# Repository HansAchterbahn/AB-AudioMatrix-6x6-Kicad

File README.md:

# AB AudioMatrix 6×6

Active audio matrix (6×6), that can map 6 input channels (1-6) to 6 output channels (A-F). Connection via 3.5 jack cable. Compatible with line signals, aux, headphones and active speakers. Each output channel can map one input channel at a time.

*Fork me and have fun!*

## 1 Content and Structure

| File / Folder                 | Abbreviation     | Description                                                                             |
| ----------------------------- | ---------------- | --------------------------------------------------------------------------------------- |
| /3d/                          | 3D models        | Files to work with in a 3D CAD program                                                  |
| /bom/                         | Bill of Material | Files with needed components and corresponding order number from different distributors |
| /case/                        | Case for PCB     | Files with an example case for the PCBs                                                 |
| /doc/                         | Documentation    | Files needed in README.md to document the repository                                    |
| /gerber/                      | Gerber files     | Files exported from Board Layout to order the PCBs from a manufacturer                  |
| /sch/                         | Schematic        | Additional schematic files                                                              |
| /AB-AudioMatrix-6x6.pro       | —                | Kicad Project File                                                                      |
| /AB-AudioMatrix-6x6.sch       | —                | Root schematic files                                                                    |
| /AB-AudioMatrix-6x6.kicad_pcb | —                | PCB / Board Layout File                                                                 |
| /LICENSE.md                   | —                | File contains project license                                                           |
| /README.md                    | —                | Markdown file with the documentation you are reading now                                |

## 2 Power Supply Modes

| Mode       | +             | —             | ⊥   | Jumper JP1 | U7, R25, R26  | Info                                                              |
| ---------- | ------------- | ------------- | --- | ---------- | ------------- | ----------------------------------------------------------------- |
| Symmetric  | +2.5 to +15 V | -2.5 to -15 V | 0V  | Open       | not necessary | Highly recommended for good Sound and clearly separated channels  |
| Asymmetric | +5 to +30 V   | 0 V           | --- | Closed     | necessary     | Possible, but not recommended; Channels are not clearly separated |

## 3 Pictures

### 3.1 Mounted device

Front view

Rear view

Bottom view

### 3.2 Board

Top view

Rear view

<!--
## 4 CAD Data

Top view

Front view

Rear view

Bottom view
-->

## 4 Schematic

Sheet 1: Root / Overview Page

Sheet 2: Switches and OPAs

Sheet 3: Audio Input and Output

## 5 Board Layout

PCB / Board layout

## 6 License

<p xmlns:dct="http://purl.org/dc/terms/" xmlns:cc="http://creativecommons.org/ns#" class="license-text"><a rel="cc:attributionURL" href="https://github.com/HansAchterbahn/AB-AudioMatrix-6x6"><span rel="dct:title">AB AudioMatrix 6×6</span></a> by <a rel="cc:attributionURL" href="https://github.com/HansAchterbahn/"><span rel="cc:attributionName">Hans Achterbahn </span></a>CC BY 4.0 </p>

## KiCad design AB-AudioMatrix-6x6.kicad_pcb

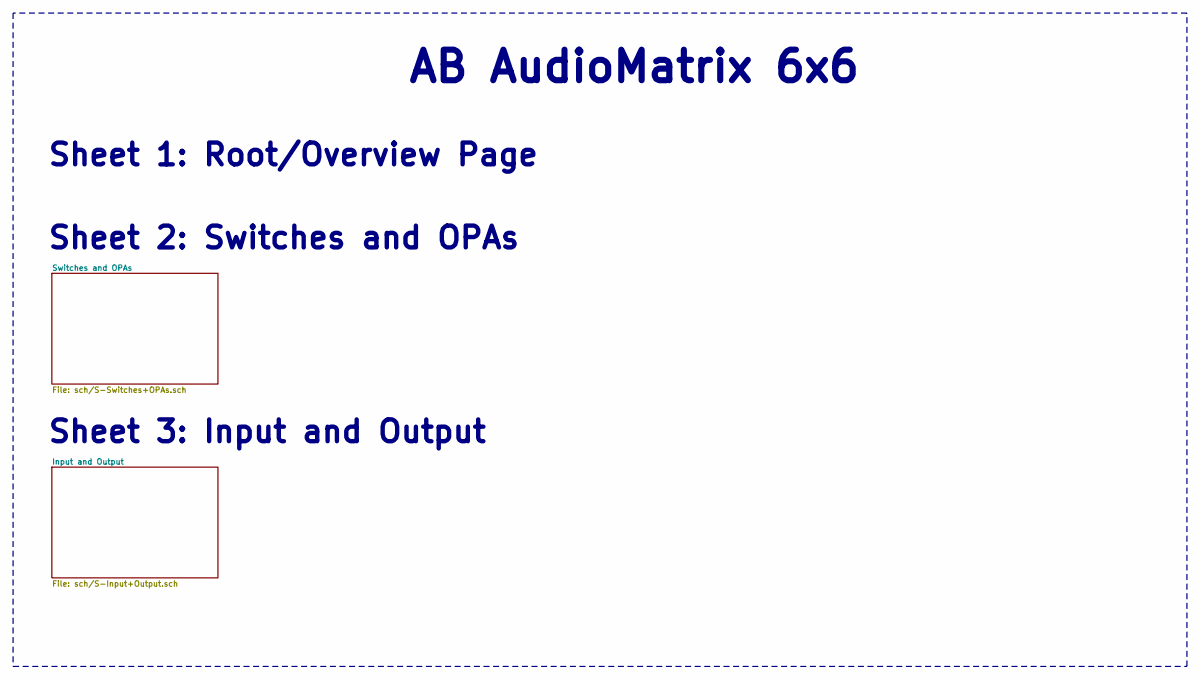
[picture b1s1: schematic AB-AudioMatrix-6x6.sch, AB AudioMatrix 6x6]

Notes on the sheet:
AB AudioMatrix 6x6
Sheet 3: Input and Output
Sheet 2: Switches and OPAs
Sheet 1: Root/Overview Page

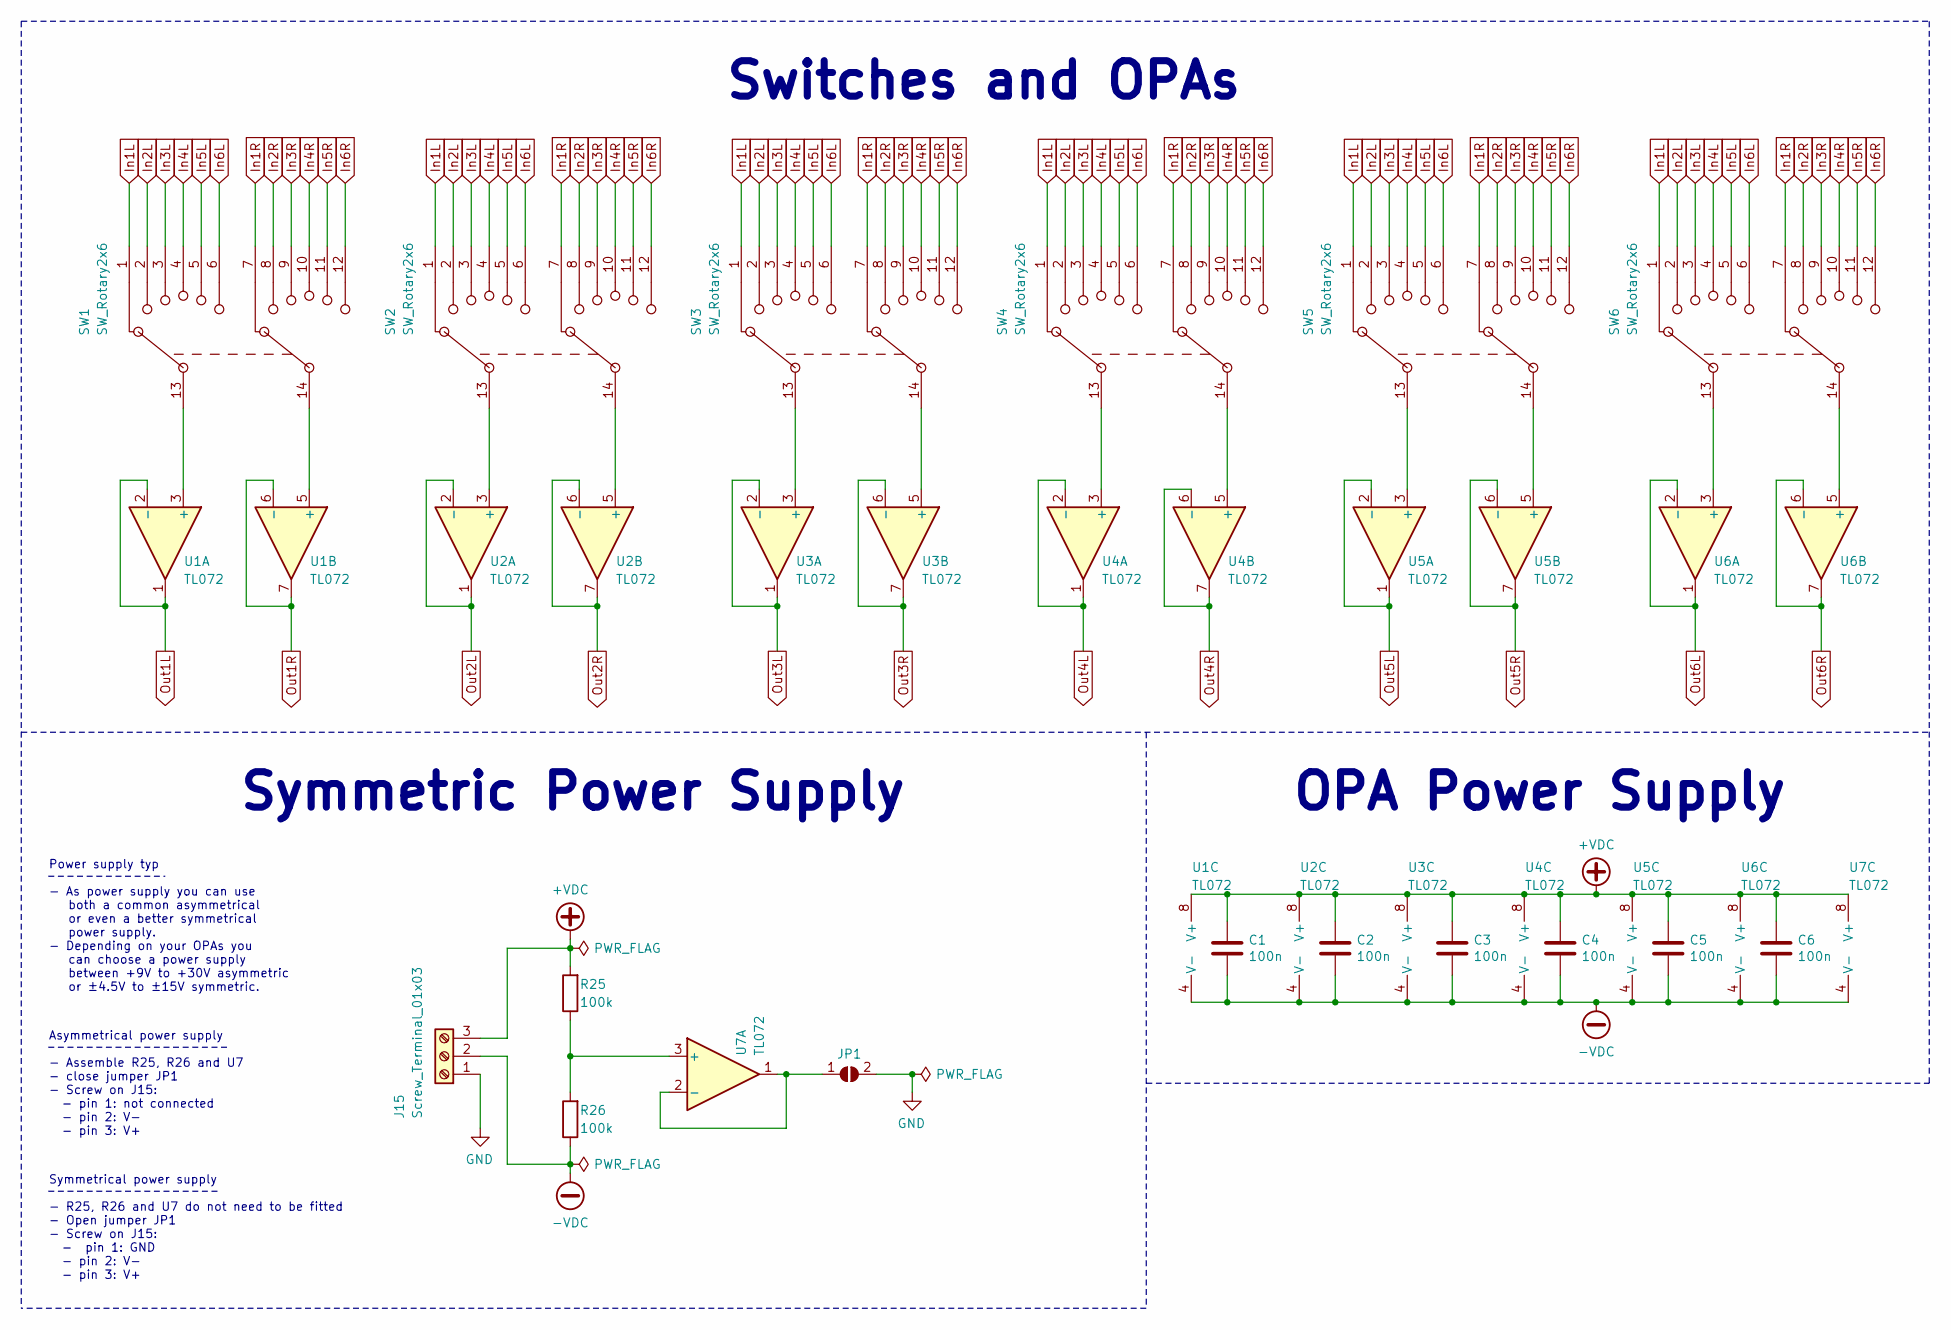
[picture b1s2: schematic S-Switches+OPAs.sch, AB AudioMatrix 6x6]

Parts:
C1, C2, C3, C4, C5, C6: 100n; C_0603_1608Metric_Pad1.05x0.95mm_HandSolder; Digi-Key 311-1779-1-ND
J15: Screw_Terminal_01x03; Wuerth-691102710003; Digi-Key 732-2029-ND
JP1: SolderJumper_2_Open; SolderJumper-2_P1.3mm_Open_TrianglePad1.0x1.5mm; Digi-Key —
R25, R26: 100k; R_0603_1608Metric_Pad1.05x0.95mm_HandSolder; Digi-Key 541-3950-1-ND
SW1, SW2, SW3, SW4, SW5, SW6: SW_Rotary2x6; CK102X06; Digi-Key —
U1, U2, U3, U4, U5, U6, U7: TL072; SOIC-8_3.9x4.9mm_P1.27mm; Digi-Key 296-1282-2-ND

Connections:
+VDC: C1.1, C2.1, C3.1, C4.1, C5.1, C6.1, J15.3, R25.2, U1.8 (V+), U2.8 (V+), U3.8 (V+), U4.8 (V+), U5.8 (V+), U6.8 (V+), U7.8 (V+)
-VDC: C1.2, C2.2, C3.2, C4.2, C5.2, C6.2, J15.2, R26.1, U1.4 (V-), U2.4 (V-), U3.4 (V-), U4.4 (V-), U5.4 (V-), U6.4 (V-), U7.4 (V-)
GND: J15.1, JP1.2 (B); also elsewhere on the board
In1L: SW1.1, SW2.1, SW3.1, SW4.1, SW5.1, SW6.1; also elsewhere on the board
In1R: SW1.7, SW2.7, SW3.7, SW4.7, SW5.7, SW6.7; also elsewhere on the board
In2L: SW1.2, SW2.2, SW3.2, SW4.2, SW5.2, SW6.2; also elsewhere on the board
In2R: SW1.8, SW2.8, SW3.8, SW4.8, SW5.8, SW6.8; also elsewhere on the board
In3L: SW1.3, SW2.3, SW3.3, SW4.3, SW5.3, SW6.3; also elsewhere on the board
In3R: SW1.9, SW2.9, SW3.9, SW4.9, SW5.9, SW6.9; also elsewhere on the board
In4L: SW1.4, SW2.4, SW3.4, SW4.4, SW5.4, SW6.4; also elsewhere on the board
In4R: SW1.10, SW2.10, SW3.10, SW4.10, SW5.10, SW6.10; also elsewhere on the board
In5L: SW1.5, SW2.5, SW3.5, SW4.5, SW5.5, SW6.5; also elsewhere on the board
In5R: SW1.11, SW2.11, SW3.11, SW4.11, SW5.11, SW6.11; also elsewhere on the board
In6L: SW1.6, SW2.6, SW3.6, SW4.6, SW5.6, SW6.6; also elsewhere on the board
In6R: SW1.12, SW2.12, SW3.12, SW4.12, SW5.12, SW6.12; also elsewhere on the board
unnamed: JP1.1 (A), U7.1, U7.2 (-)
unnamed: R25.1, R26.2, U7.3 (+)
unnamed: SW1.13, U1.3 (+)
unnamed: SW1.14, U1.5 (+)
unnamed: SW2.13, U2.3 (+)
unnamed: SW2.14, U2.5 (+)
unnamed: SW3.13, U3.3 (+)
unnamed: SW3.14, U3.5 (+)
unnamed: SW4.13, U4.3 (+)
unnamed: SW4.14, U4.5 (+)
unnamed: SW5.13, U5.3 (+)
unnamed: SW5.14, U5.5 (+)
unnamed: SW6.13, U6.3 (+)
unnamed: SW6.14, U6.5 (+)
Out1L: U1.1, U1.2 (-); also elsewhere on the board
Out1R: U1.6 (-), U1.7; also elsewhere on the board
Out2L: U2.1, U2.2 (-); also elsewhere on the board
Out2R: U2.6 (-), U2.7; also elsewhere on the board
Out3L: U3.1, U3.2 (-); also elsewhere on the board
Out3R: U3.6 (-), U3.7; also elsewhere on the board
Out4L: U4.1, U4.2 (-); also elsewhere on the board
Out4R: U4.6 (-), U4.7; also elsewhere on the board
Out5L: U5.1, U5.2 (-); also elsewhere on the board
Out5R: U5.6 (-), U5.7; also elsewhere on the board
Out6L: U6.1, U6.2 (-); also elsewhere on the board
Out6R: U6.6 (-), U6.7; also elsewhere on the board

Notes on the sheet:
Switches and OPAs
OPA Power Supply
Symmetric Power Supply
Symmetrical power supply - R25, R26 and U7 do not need to be fitted - Open jumper JP1 - Screw on J15: - pin 1: GND - pin 2: V- - pin 3: V+
Asymmetrical power supply - Assemble R25, R26 and U7 - close jumper JP1 - Screw on J15: - pin 1: not connected - pin 2: V- - pin 3: V+
Power supply typ - As power supply you can use both a common asymmetrical or even a better symmetrical power supply. - Depending on your OPAs you can choose a power supply between +9V to +30V asymmetric or ±4.5V to ±15V symmetric.

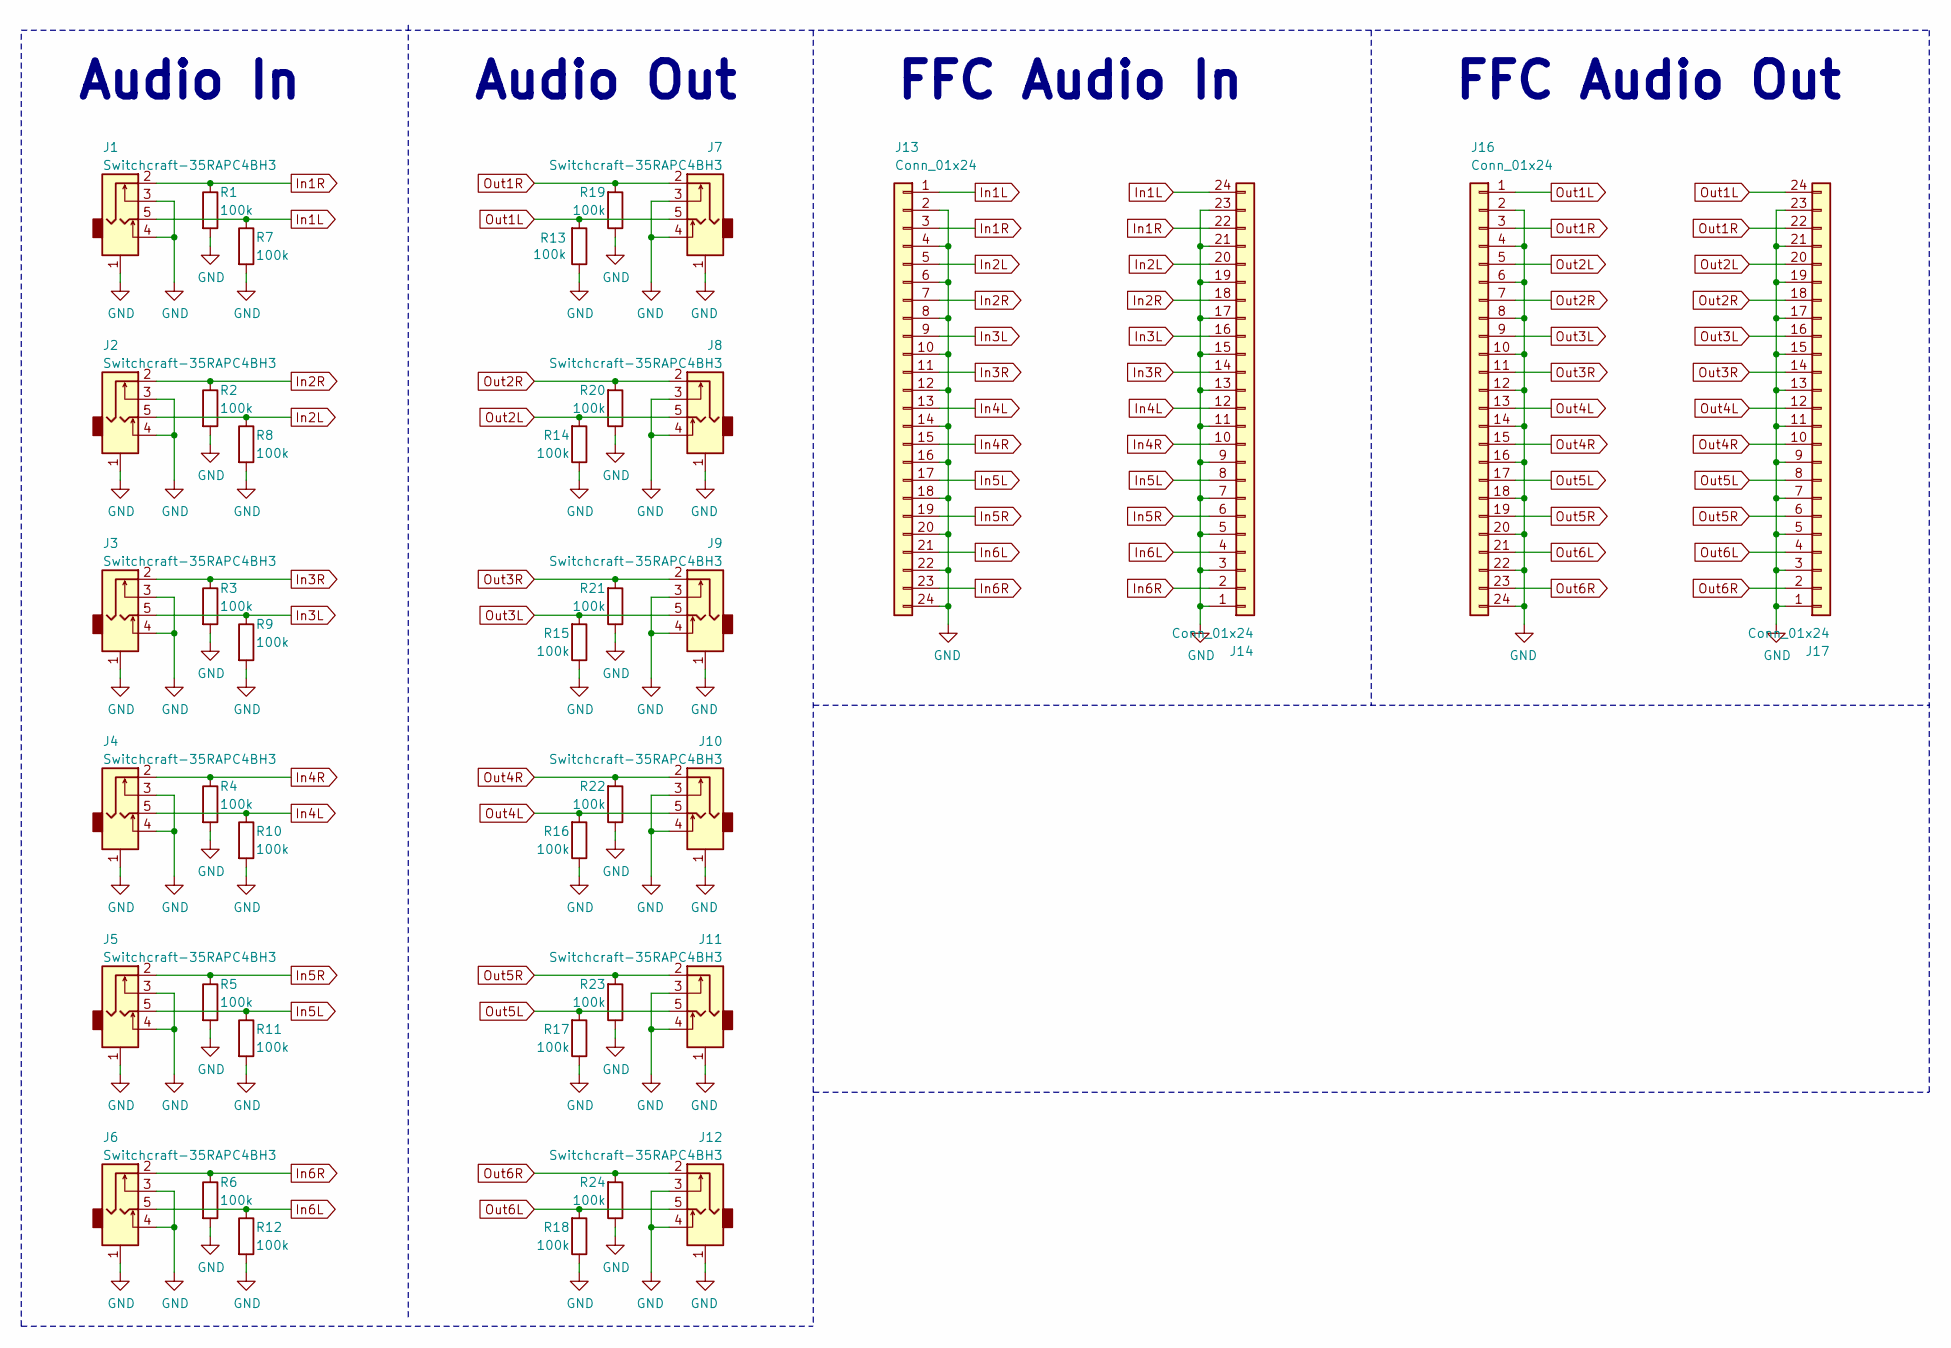
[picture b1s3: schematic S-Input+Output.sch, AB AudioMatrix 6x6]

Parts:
J1, J2, J3, J4, J5, J6, J7, J8, J9, J10, J11, J12: Switchcraft-35RAPC4BH3; Digi-Key SC1464-ND
J13, J14, J16, J17: Conn_01x24; Wuerth-686124188622; Digi-Key 732-686124188622CT-ND
R1, R2, R3, R4, R5, R6, R7, R8, R9, R10, R11, R12, R13, R14, R15, R16, R17, R18, R19, R20, R21, R22, R23, R24: 100k; R_0603_1608Metric_Pad1.05x0.95mm_HandSolder; Digi-Key 541-3950-1-ND

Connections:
GND: J1.1, J1.3, J1.4, J2.1, J2.3, J2.4, J3.1, J3.3, J3.4, J4.1, J4.3, J4.4, J5.1, J5.3, J5.4, J6.1, J6.3, J6.4, J7.1, J7.3, J7.4, J8.1, J8.3, J8.4, J9.1, J9.3, J9.4, J10.1, J10.3, J10.4, J11.1, J11.3, J11.4, J12.1, J12.3, J12.4, J13.2, J13.4, J13.6, J13.8, J13.10, J13.12, J13.14, J13.16, J13.18, J13.20, J13.22, J13.24, J14.1, J14.3, J14.5, J14.7, J14.9, J14.11, J14.13, J14.15, J14.17, J14.19, J14.21, J14.23, J16.2, J16.4, J16.6, J16.8, J16.10, J16.12, J16.14, J16.16, J16.18, J16.20, J16.22, J16.24, J17.1, J17.3, J17.5, J17.7, J17.9, J17.11, J17.13, J17.15, J17.17, J17.19, J17.21, J17.23, R1.2, R2.2, R3.2, R4.2, R5.2, R6.2, R7.2, R8.2, R9.2, R10.2, R11.2, R12.2, R13.1, R14.1, R15.1, R16.1, R17.1, R18.1, R19.1, R20.1, R21.1, R22.1, R23.1, R24.1; also elsewhere on the board
In1L: J1.5, J13.1, J14.24, R7.1; also elsewhere on the board
In1R: J1.2, J13.3, J14.22, R1.1; also elsewhere on the board
In2L: J2.5, J13.5, J14.20, R8.1; also elsewhere on the board
In2R: J2.2, J13.7, J14.18, R2.1; also elsewhere on the board
In3L: J3.5, J13.9, J14.16, R9.1; also elsewhere on the board
In3R: J3.2, J13.11, J14.14, R3.1; also elsewhere on the board
In4L: J4.5, J13.13, J14.12, R10.1; also elsewhere on the board
In4R: J4.2, J13.15, J14.10, R4.1; also elsewhere on the board
In5L: J5.5, J13.17, J14.8, R11.1; also elsewhere on the board
In5R: J5.2, J13.19, J14.6, R5.1; also elsewhere on the board
In6L: J6.5, J13.21, J14.4, R12.1; also elsewhere on the board
In6R: J6.2, J13.23, J14.2, R6.1; also elsewhere on the board
Out1L: J7.5, J16.1, J17.24, R13.2; also elsewhere on the board
Out1R: J7.2, J16.3, J17.22, R19.2; also elsewhere on the board
Out2L: J8.5, J16.5, J17.20, R14.2; also elsewhere on the board
Out2R: J8.2, J16.7, J17.18, R20.2; also elsewhere on the board
Out3L: J9.5, J16.9, J17.16, R15.2; also elsewhere on the board
Out3R: J9.2, J16.11, J17.14, R21.2; also elsewhere on the board
Out4L: J10.5, J16.13, J17.12, R16.2; also elsewhere on the board
Out4R: J10.2, J16.15, J17.10, R22.2; also elsewhere on the board
Out5L: J11.5, J16.17, J17.8, R17.2; also elsewhere on the board
Out5R: J11.2, J16.19, J17.6, R23.2; also elsewhere on the board
Out6L: J12.5, J16.21, J17.4, R18.2; also elsewhere on the board
Out6R: J12.2, J16.23, J17.2, R24.2; also elsewhere on the board

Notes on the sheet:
Audio In
Audio Out
FFC Audio In
FFC Audio Out

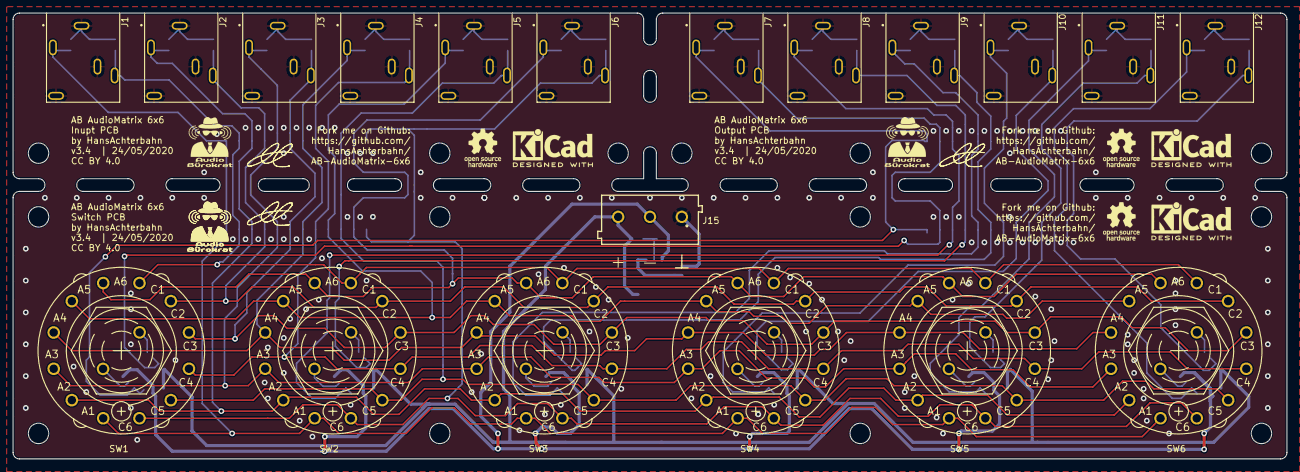
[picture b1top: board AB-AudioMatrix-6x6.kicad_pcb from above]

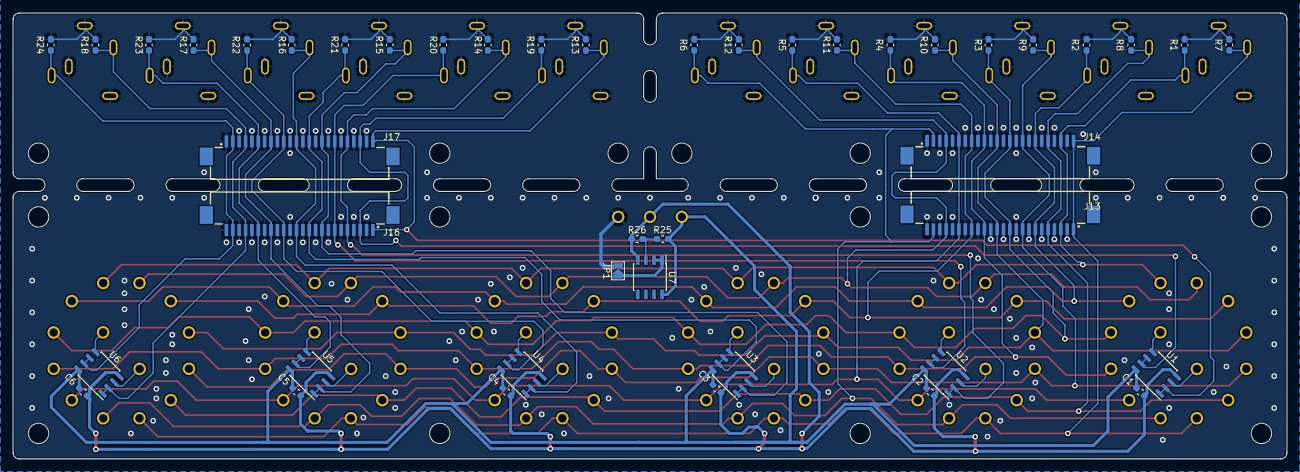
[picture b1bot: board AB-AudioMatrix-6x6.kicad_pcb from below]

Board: 4 copper layers, 200.0 x 70.0 mm, 63 parts (44 on the bottom side), 41 nets.

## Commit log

2020-05-12 Complete schematic | started PCB
2020-05-12 Added README and LICENCE
2020-05-13 added Edge.Cuts | devices arranged on PCB | added GND planes
2020-05-14 added converter for asymmetric power supply | Routing In & Out PCB finished | Routing Switch PCB started
2020-05-16 Routing switches complete
2020-05-16 Routing Input FFC connector to switches
2020-05-17 swaped supply pins | routing complete → routing revision and optimization necessary
2020-05-18 finished routing | added GND polygon | added description in surface plot | added pictures to README.md documentation | changed LICENCE.md to CC BY 4.0
2020-05-18 added gitignore
2020-05-18 Date updated and Github link added to schematic and board
2020-05-24 added new attributes MF, MFN, Mouser, Digi-Key, RS-Online, Infopage, datasheet | bill of material (BOM) created | infobox updated | added AudioBürokrat logo on silkscreen
2020-05-24 Added BOM files in .gitignore
2020-05-25 changed AudioBürokrat logo
2020-05-25 removed unwanted files
2020-05-25 added folder for BOM
2020-05-25 changed AudioBürokrat logo (Bitmap import)
2020-05-25 renamed doku folder to doc |updated README.md and some pictures in doc folder
2020-05-25 moved additional schematic sheets to folder sch | updated README.md
2020-05-25 updated schematic
2020-05-25 updated .gitignore
2020-05-25 Gerber files generated
2020-05-25 changed 3D path for some footprints on PCB | started 3D Model in FreeCAD
2020-06-22 Update README.md → added PCB pictures | added chapter _Power Supply_
2020-06-22 Update README.md → changed parts in _Power Supply_ | croped first picture
2020-07-24 Changed 3d Model | added 3D STL Format | added Lasercutter Case
2020-07-24 Documentation: Optimized a picture
2020-07-24 Updated AudioBürokrat Logo
2020-07-28 optimized lasercutter case
2020-09-04 laser cutter case: added cuts for switch and power cable
2020-09-05 laser cutter case: cut tested + tiny optimization + deleted unused parts
2020-09-06 README.md: Added pics of mounted device | pics exposed from surroundings | small optimizations

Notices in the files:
AB-AudioMatrix-6x6.kicad_pcb:
Licence: CC BY 4.0 (https://creativecommons.org/licenses/by/4.0/)
